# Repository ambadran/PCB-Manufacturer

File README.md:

# PCB-Manufacturer

###  Intro
A cnc machine with a kinematic mounting mechanism and specialised code to change head as wanted so as to have access to all the
tools to create a PCB without any human intervention.

### Mechanics
This is a 3 Axis CNC machine made of both metal and 3D printed Parts.
The main driving mechanism is a V-wheel on 2020 profile system with a GT-2 belt driving.
Nema17 Motors was used. The machine was designed for maximal repeatability. 

A 3D printed Kinematic Mounting System was developed to enable the CNC machine to detach and attach to different tool heads on command. The current tool heads are a laser head, a spindle, a Pen marker. The machine automatically attaches to the wanted tool heads without any human intervention.

I also developed an auto-clamping system that clamps the PCB in the bed automatically.

#### Photos

### Electronics
The Main MCU is an Arduino Mega. A Custom GRBL firmware created by me is running on it.

To add a screen monitoring functionality and control the main MCU wirelessly through WiFi, I added a raspberry pi 4 with a 7 inch screen, running mainly UGS Software to monitor the CNC machine.

The Stepper drivers are powerful TB6600 drivers, The end-stops have their own opto-coupler circuit. 
There are 3 power supplies for the CNC machine. one 5v for the main MCU only, one 5v for the raspberry pi. and the third 24v is for the rest of the CNC machine.

This main 24v power supply is switched on using a relay that is controled by the Main MCU. A special G-Code was coded in the firmware to control the main power supply. This adds an important safety layer as the machine is intended to be run remotely.

To relieve the Main MCU from doing everything in the project. I took the liberity to make different circuits for different functions needed for this machine.

I developed a circuit that takes in a 3-bit binary code and the spindle PWM signal from the Main MCU. Then it decodes the 3-bit binary code to allow the PWM to exit through one of the 8 channels that this CNC machine controls. Meaning, the machine can control 8 different end-effectors with PWM, depending on the current 3-bit binary that the MCU outputs.

Another circuit worth mentioning was the stand alone circuit to control the latching mechanism of the kinematic mounting system, where the input to the circuit is just a HIGH/LOW signal from the main MCU triggered by a G-code command `A1` or `A0`. The local MCU does controls the unipolar stepper to latch ON or OFF to the Female kinematic mounts on command and does all the necessary closed-loop logic locally.

### Programming
I customized the GRBL firmware from: https://github.com/gnea/grbl 
To accomodate for all the new functionality needed for this CNC machine.
I put in my own G-code commands like `A<x>`, `B<x>` or `C<x>`, that outputs the necessary logic on the Main MCU GPIOs, with no compromise to the original code.

I also developed (from scratch) a complete CAM solution that takes in the gerber files and gives out the G-code ready for my machine. However, due to me deciding to develop from scratch and not use geometry-manipulating libraries like `shapely`. There is alot of corner cases that this version can't handle. 
However, I developed V2 of my all-in-one CAM solution for my CNC machine here: https://github.com/ambadran/PCB-CAM

This version is much much more reliable as to it not being built from scratch.

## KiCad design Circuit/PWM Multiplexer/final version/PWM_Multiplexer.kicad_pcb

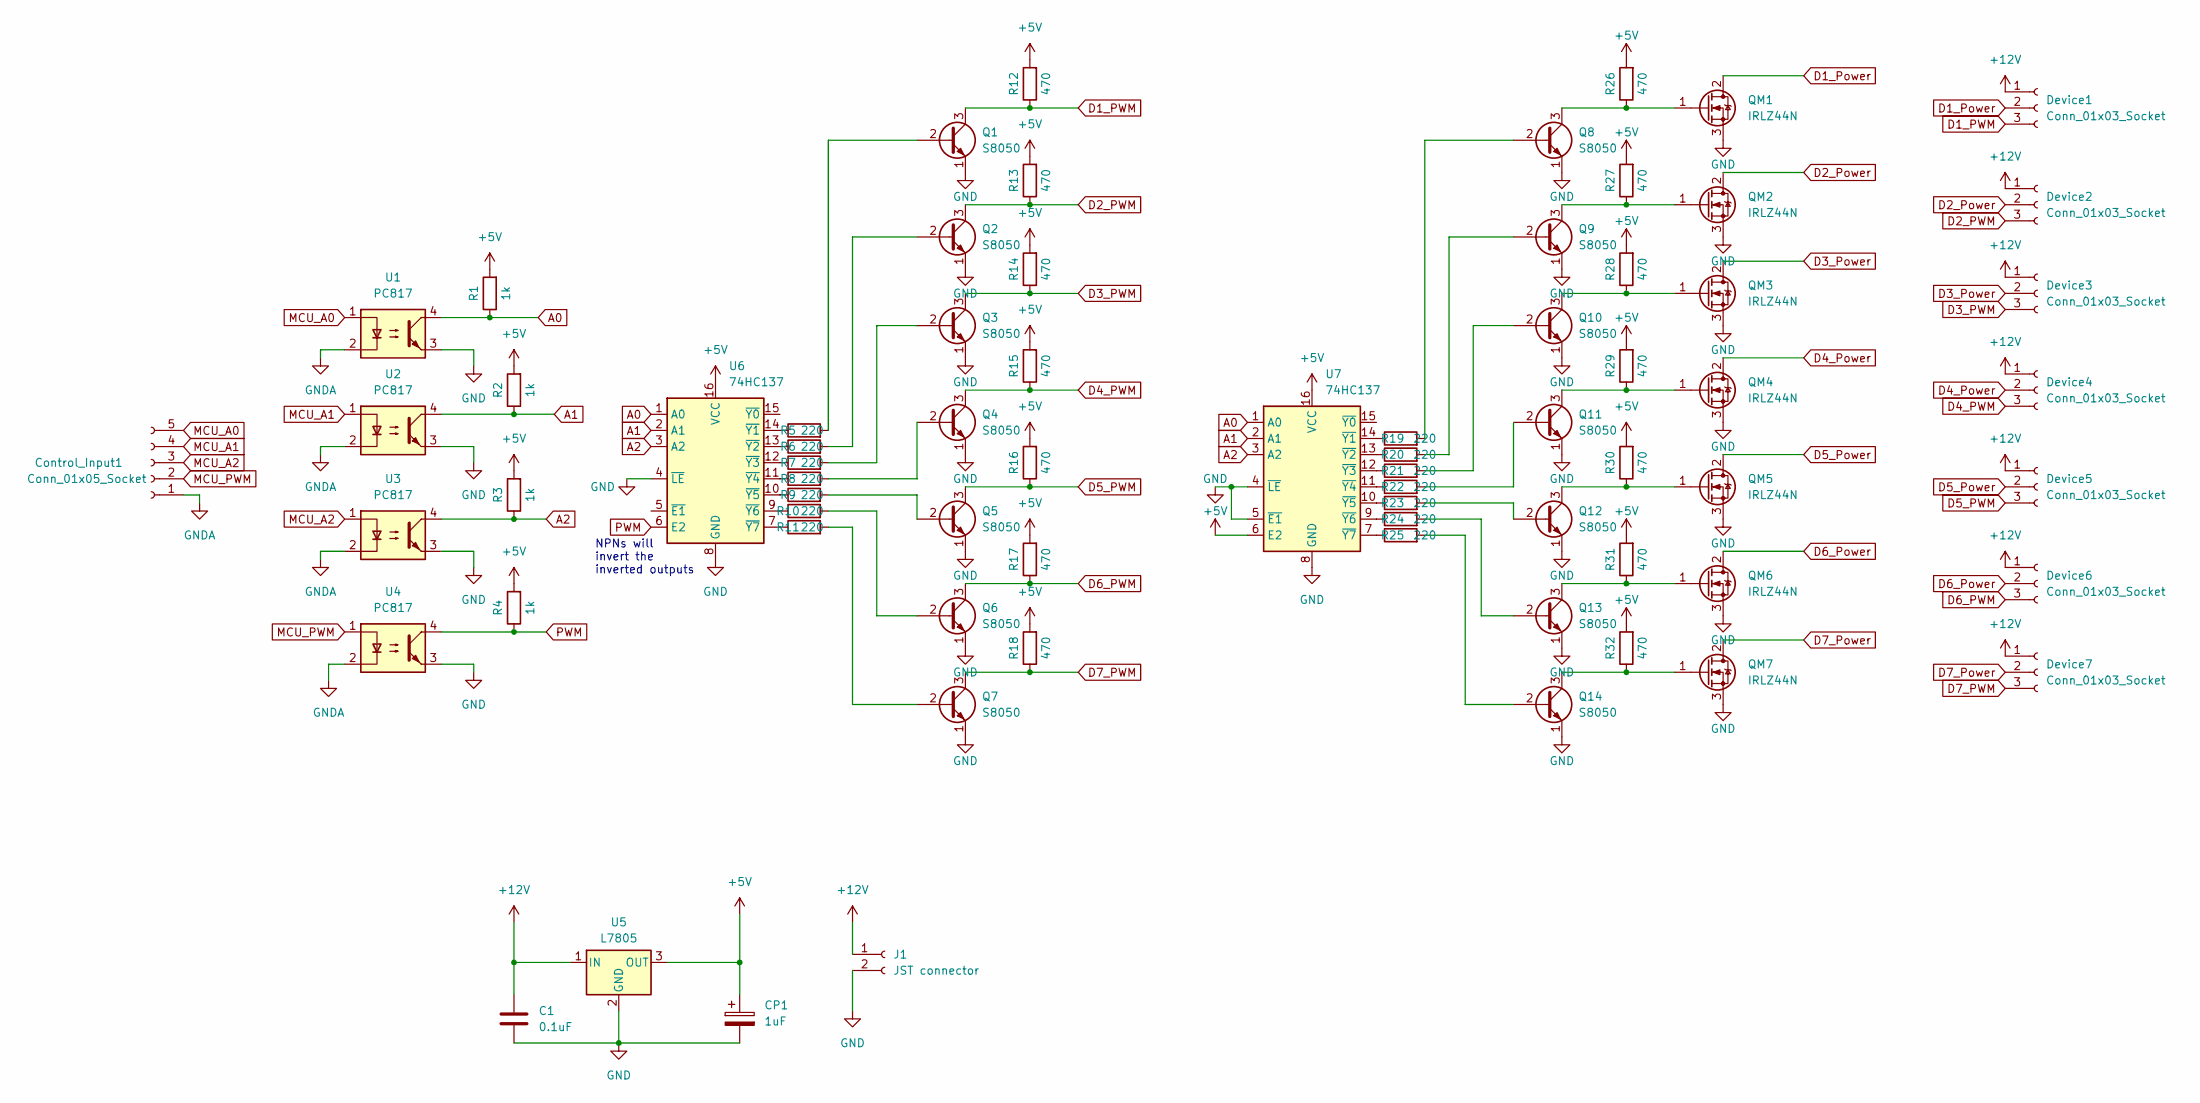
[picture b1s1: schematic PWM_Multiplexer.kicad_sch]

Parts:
C1: 0.1uF; C_Disc_D5.0mm_W2.5mm_P2.50mm
CP1: 1uF; CP_Radial_D5.0mm_P2.50mm
Control_Input1: Conn_01x05_Socket; JST_EH_S5B-EH_1x05_P2.50mm_Horizontal
Device1, Device2, Device3, Device4, Device5, Device6, Device7: Conn_01x03_Socket; JST_EH_S3B-EH_1x03_P2.50mm_Horizontal
J1: JST connector; JST_EH_S2B-EH_1x02_P2.50mm_Horizontal
Q1, Q2, Q3, Q4, Q5, Q6, Q7, Q8, Q9, Q10, Q11, Q12, Q13, Q14: S8050; TO-92_Inline
QM1, QM2, QM3, QM4, QM5, QM6, QM7: IRLZ44N; TO-220-3_Vertical
R1, R2, R3, R4: 1k; R_Axial_DIN0207_L6.3mm_D2.5mm_P7.62mm_Horizontal
R5, R6, R7, R8, R9, R10, R11: 220; R_Axial_DIN0207_L6.3mm_D2.5mm_P10.16mm_Horizontal
R12, R13, R14, R15, R16, R17, R18: 470; R_Axial_DIN0207_L6.3mm_D2.5mm_P7.62mm_Horizontal
R19, R20, R21, R22, R23, R24, R25: 220; R_Axial_DIN0207_L6.3mm_D2.5mm_P7.62mm_Horizontal
R26, R27, R28, R29, R30, R31, R32: 470; R_Axial_DIN0207_L6.3mm_D2.5mm_P10.16mm_Horizontal
U1, U2, U3, U4: PC817; DIP-4_W7.62mm
U5: L7805; TO-220-3_Vertical
U6, U7: 74HC137; DIP-16_W7.62mm_Socket_LongPads

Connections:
+5V: CP1.1, R1.2, R2.2, R3.2, R4.2, R12.2, R13.2, R14.2, R15.2, R16.2, R17.2, R18.2, R26.2, R27.2, R28.2, R29.2, R30.2, R31.2, R32.2, U5.3 (OUT), U6.16 (VCC), U7.6 (E2), U7.16 (VCC)
+12V: C1.1, Device1.1, Device2.1, Device3.1, Device4.1, Device5.1, Device6.1, Device7.1, J1.1, U5.1 (IN)
A0: R1.1, U1.4, U6.1 (A0), U7.1 (A0)
A1: R2.1, U2.4, U6.2 (A1), U7.2 (A1)
A2: R3.1, U3.4, U6.3 (A2), U7.3 (A2)
D1_PWM: Device1.3, Q1.3 (C), R12.1
D1_Power: Device1.2, QM1.2 (D)
D2_PWM: Device2.3, Q2.3 (C), R13.1
D2_Power: Device2.2, QM2.2 (D)
D3_PWM: Device3.3, Q3.3 (C), R14.1
D3_Power: Device3.2, QM3.2 (D)
D4_PWM: Device4.3, Q4.3 (C), R15.1
D4_Power: Device4.2, QM4.2 (D)
D5_PWM: Device5.3, Q5.3 (C), R16.1
D5_Power: Device5.2, QM5.2 (D)
D6_PWM: Device6.3, Q6.3 (C), R17.1
D6_Power: Device6.2, QM6.2 (D)
D7_PWM: Device7.3, Q7.3 (C), R18.1
D7_Power: Device7.2, QM7.2 (D)
GND: C1.2, CP1.2, J1.2, Q1.1 (E), Q2.1 (E), Q3.1 (E), Q4.1 (E), Q5.1 (E), Q6.1 (E), Q7.1 (E), Q8.1 (E), Q9.1 (E), Q10.1 (E), Q11.1 (E), Q12.1 (E), Q13.1 (E), Q14.1 (E), QM1.3 (S), QM2.3 (S), QM3.3 (S), QM4.3 (S), QM5.3 (S), QM6.3 (S), QM7.3 (S), U1.3, U2.3, U3.3, U4.3, U5.2 (GND), U6.4 (~LE), U6.8 (GND), U7.4 (~LE), U7.5 (~E1), U7.8 (GND)
GNDA: Control_Input1.1, U1.2, U2.2, U3.2, U4.2
MCU_A0: Control_Input1.5, U1.1
MCU_A1: Control_Input1.4, U2.1
MCU_A2: Control_Input1.3, U3.1
MCU_PWM: Control_Input1.2, U4.1
unnamed: Q1.2 (B), R5.2
unnamed: Q2.2 (B), R6.2
unnamed: Q3.2 (B), R7.2
unnamed: Q4.2 (B), R8.2
unnamed: Q5.2 (B), R9.2
unnamed: Q6.2 (B), R10.2
unnamed: Q7.2 (B), R11.2
unnamed: Q8.2 (B), R19.2
unnamed: Q8.3 (C), QM1.1 (G), R26.1
unnamed: Q9.2 (B), R20.2
unnamed: Q9.3 (C), QM2.1 (G), R27.1
unnamed: Q10.2 (B), R21.2
unnamed: Q10.3 (C), QM3.1 (G), R28.1
unnamed: Q11.2 (B), R22.2
unnamed: Q11.3 (C), QM4.1 (G), R29.1
unnamed: Q12.2 (B), R23.2
unnamed: Q12.3 (C), QM5.1 (G), R30.1
unnamed: Q13.2 (B), R24.2
unnamed: Q13.3 (C), QM6.1 (G), R31.1
unnamed: Q14.2 (B), R25.2
unnamed: Q14.3 (C), QM7.1 (G), R32.1
unnamed: R5.1, U6.14 (~Y1)
unnamed: R6.1, U6.13 (~Y2)
unnamed: R7.1, U6.12 (~Y3)
unnamed: R8.1, U6.11 (~Y4)
unnamed: R9.1, U6.10 (~Y5)
unnamed: R10.1, U6.9 (~Y6)
unnamed: R11.1, U6.7 (~Y7)
unnamed: R19.1, U7.14 (~Y1)
unnamed: R20.1, U7.13 (~Y2)
unnamed: R21.1, U7.12 (~Y3)
unnamed: R22.1, U7.11 (~Y4)
unnamed: R23.1, U7.10 (~Y5)
unnamed: R24.1, U7.9 (~Y6)
unnamed: R25.1, U7.7 (~Y7)
PWM: R4.1, U4.4, U6.6 (E2)

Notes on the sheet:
NPNs will invert the inverted outputs

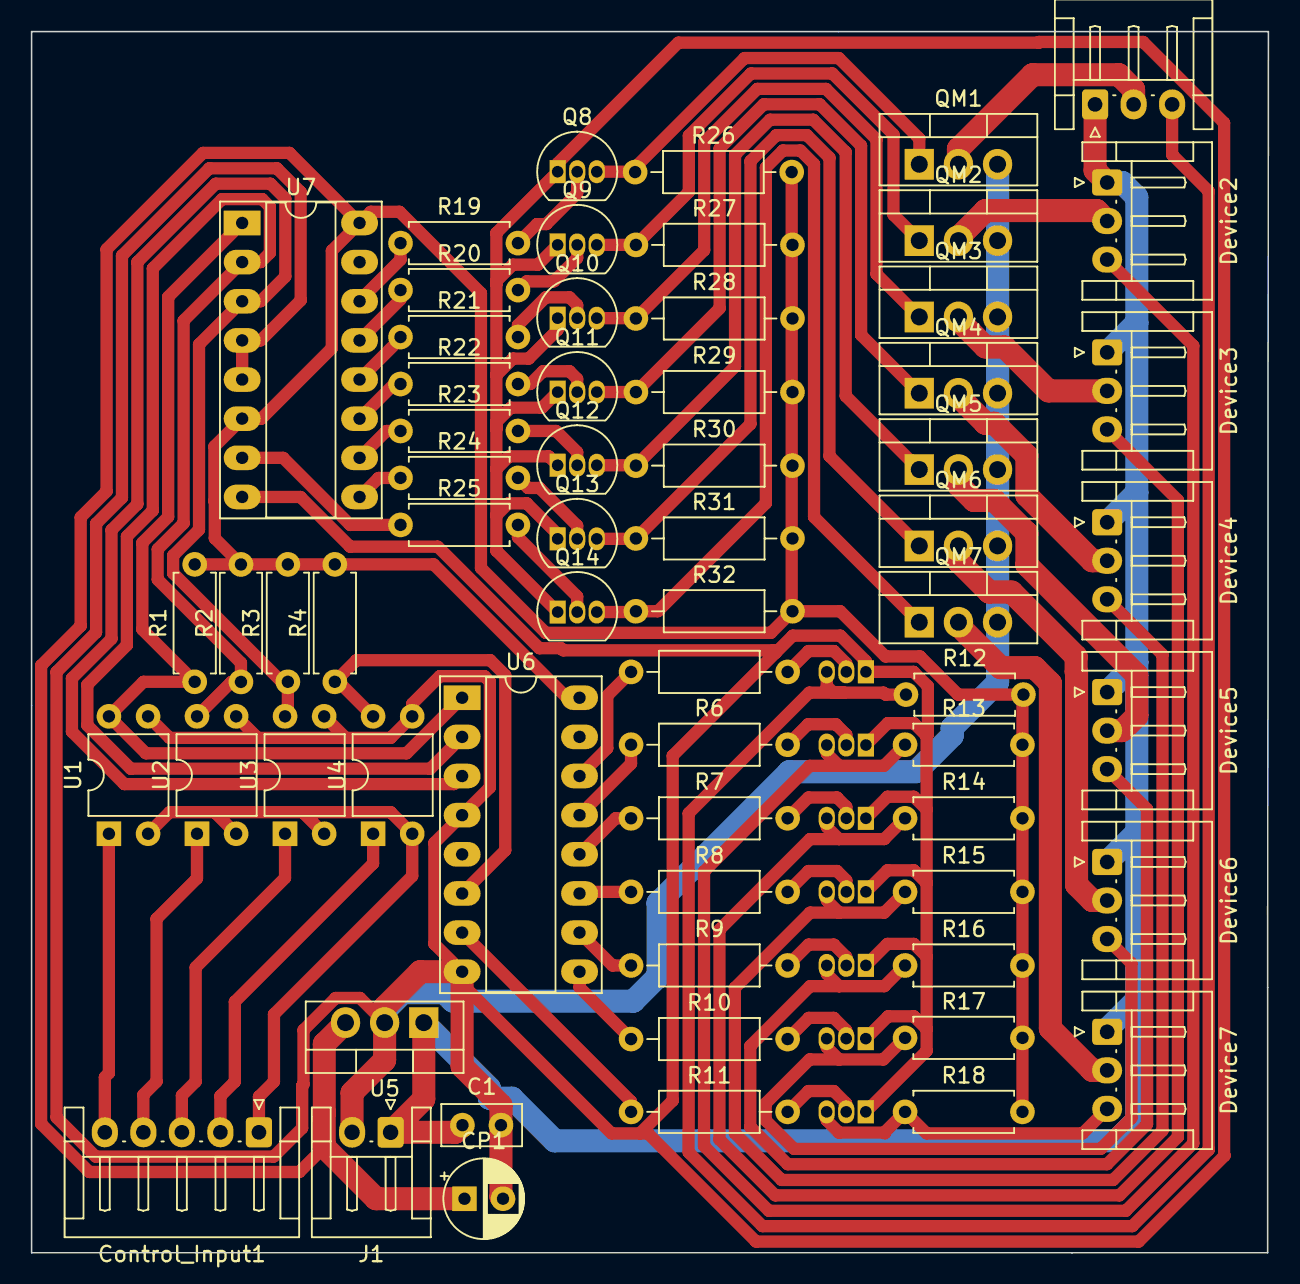
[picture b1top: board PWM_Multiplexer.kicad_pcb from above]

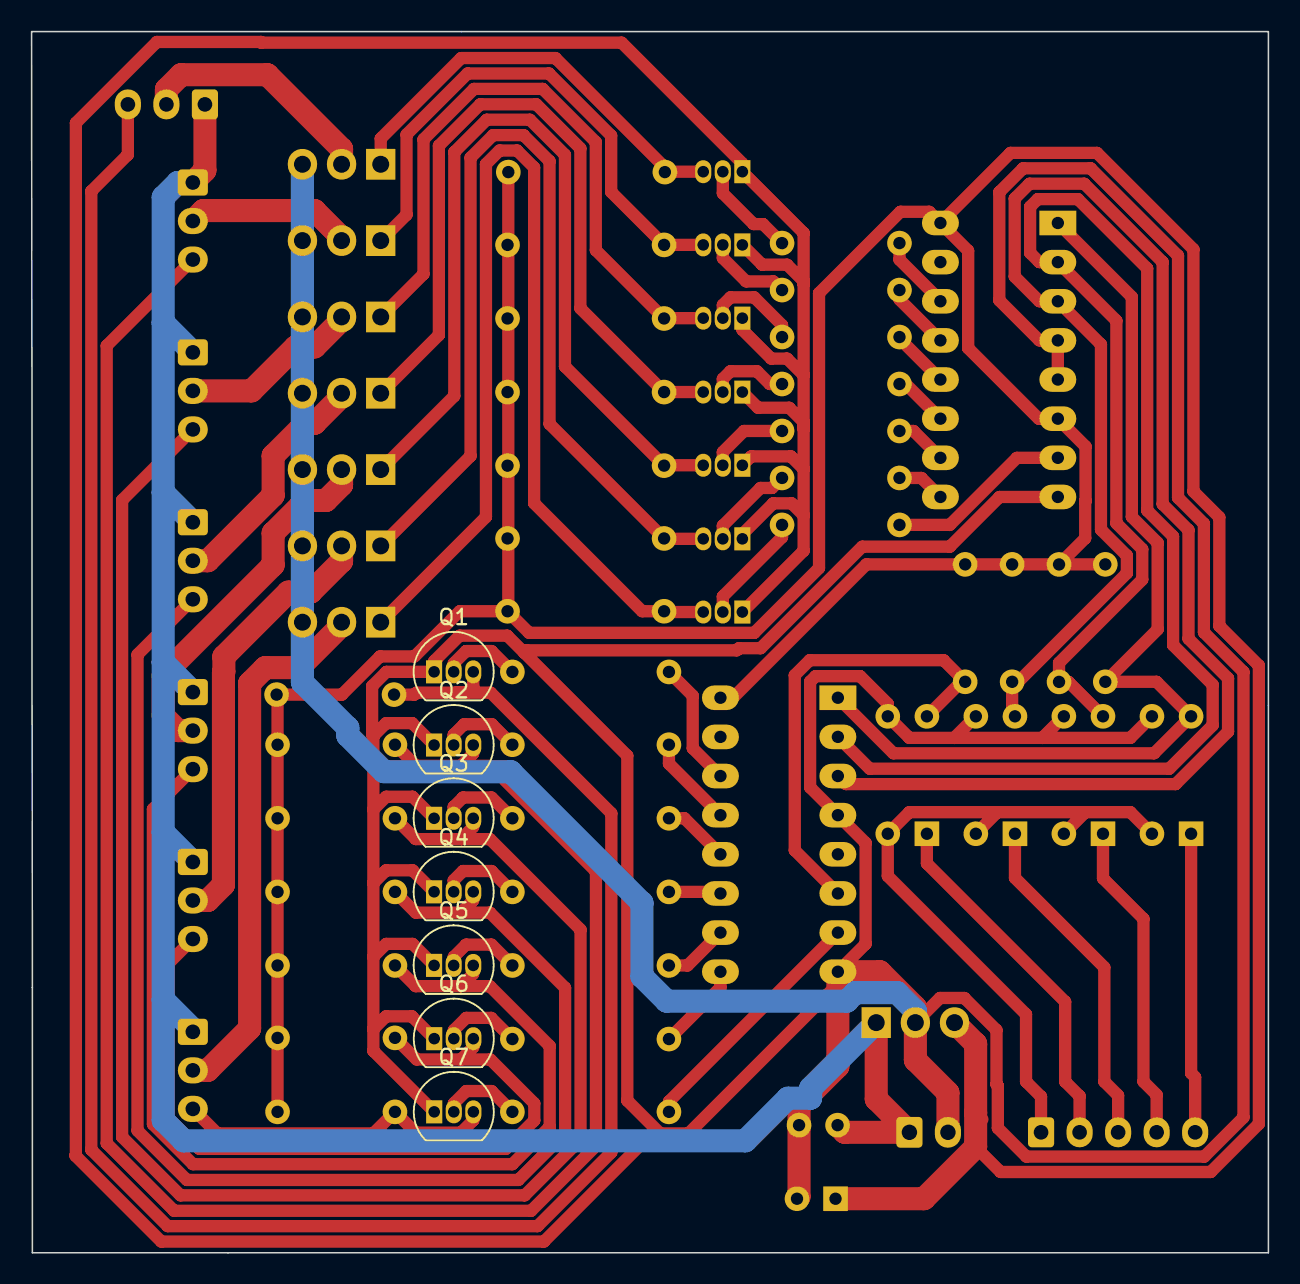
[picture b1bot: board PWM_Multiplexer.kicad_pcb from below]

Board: 2 copper layers, 80.3 x 79.2 mm, 71 parts (7 on the bottom side), 61 nets.

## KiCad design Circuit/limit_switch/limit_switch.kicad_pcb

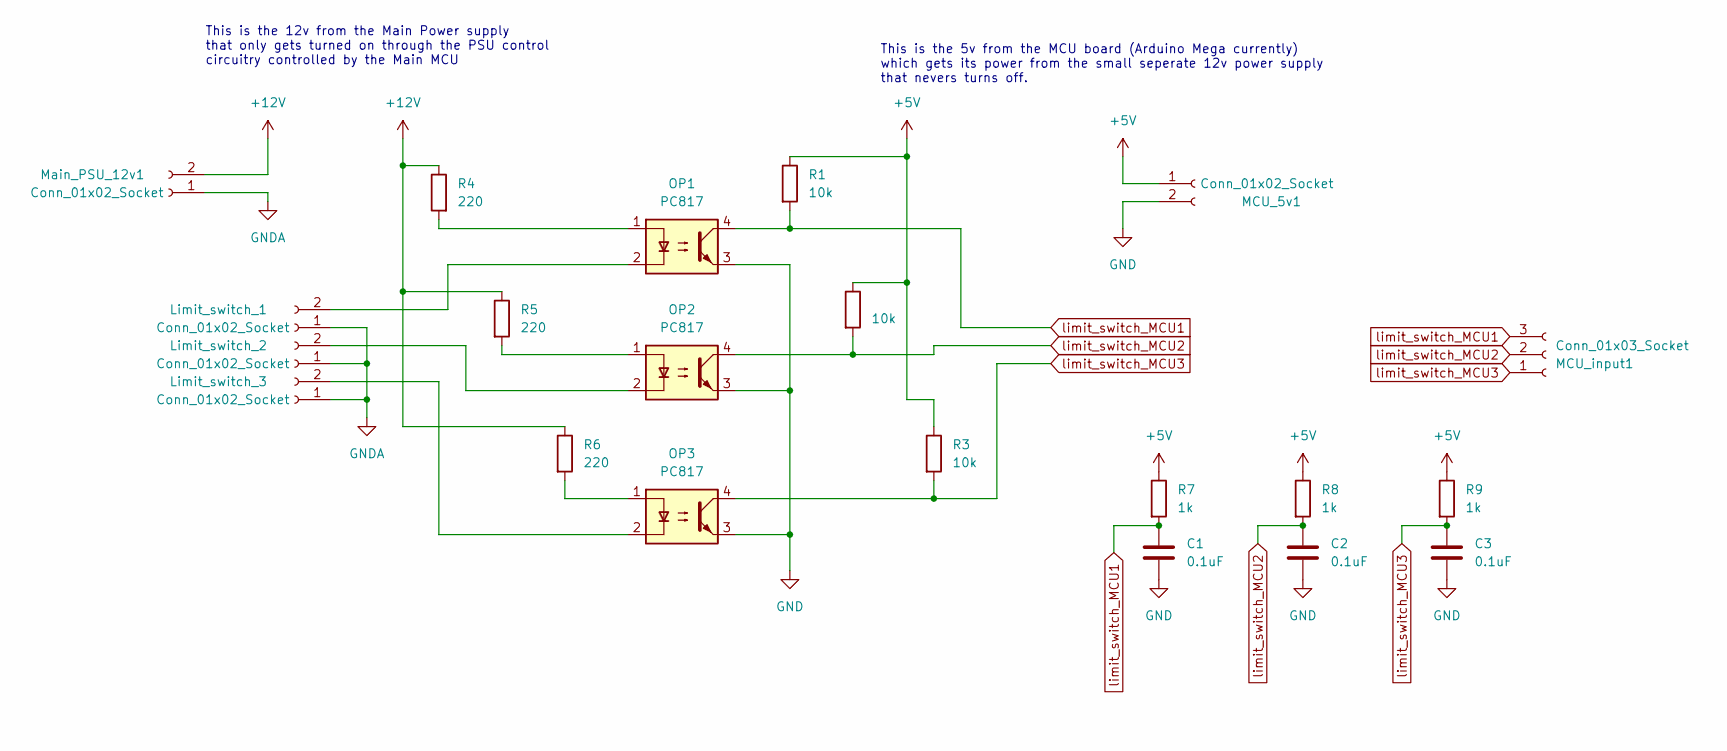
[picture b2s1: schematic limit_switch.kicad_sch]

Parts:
C1, C2, C3: 0.1uF; C_Disc_D5.0mm_W2.5mm_P5.00mm
Limit_switch_1, Limit_switch_2, Limit_switch_3: Conn_01x02_Socket; JST_EH_S2B-EH_1x02_P2.50mm_Horizontal
MCU_5v1: Conn_01x02_Socket; JST_EH_S2B-EH_1x02_P2.50mm_Horizontal
MCU_input1: Conn_01x03_Socket; JST_EH_S3B-EH_1x03_P2.50mm_Horizontal
Main_PSU_12v1: Conn_01x02_Socket; JST_EH_S2B-EH_1x02_P2.50mm_Horizontal
OP1, OP2, OP3: PC817; DIP-4_W7.62mm
R1, R2, R3: 10k; R_Axial_DIN0207_L6.3mm_D2.5mm_P7.62mm_Horizontal
R4, R5, R6: 220; R_Axial_DIN0207_L6.3mm_D2.5mm_P7.62mm_Horizontal
R7, R8, R9: 1k; R_Axial_DIN0207_L6.3mm_D2.5mm_P7.62mm_Horizontal

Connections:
+5V: MCU_5v1.1, R1.1, R2.1, R3.1, R7.1, R8.1, R9.1
+12V: Main_PSU_12v1.2, R4.1, R5.1, R6.1
GND: C1.2, C2.2, C3.2, MCU_5v1.2, OP1.3, OP2.3, OP3.3
GNDA: Limit_switch_1.1, Limit_switch_2.1, Limit_switch_3.1, Main_PSU_12v1.1
unnamed: Limit_switch_1.2, OP1.2
unnamed: Limit_switch_2.2, OP2.2
unnamed: Limit_switch_3.2, OP3.2
unnamed: OP1.1, R4.2
unnamed: OP2.1, R5.2
unnamed: OP3.1, R6.2
limit_switch_MCU1: C1.1, MCU_input1.3, OP1.4, R1.2, R7.2
limit_switch_MCU2: C2.1, MCU_input1.2, OP2.4, R2.2, R8.2
limit_switch_MCU3: C3.1, MCU_input1.1, OP3.4, R3.2, R9.2

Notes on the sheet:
This is the 12v from the Main Power supply that only gets turned on through the PSU control circuitry controlled by the Main MCU
This is the 5v from the MCU board (Arduino Mega currently) which gets its power from the small seperate 12v power supply that nevers turns off.

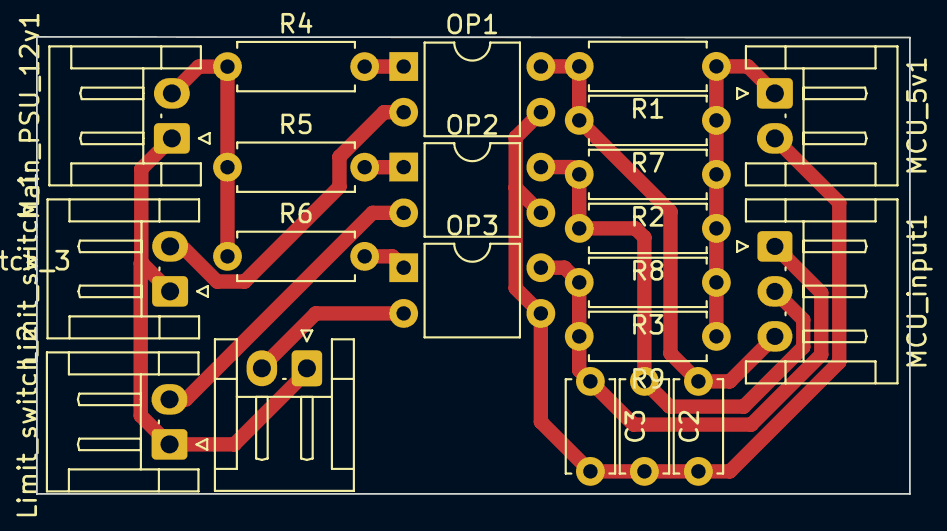
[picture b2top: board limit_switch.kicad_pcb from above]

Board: 2 copper layers, 48.5 x 25.4 mm, 21 parts (0 on the bottom side), 13 nets.

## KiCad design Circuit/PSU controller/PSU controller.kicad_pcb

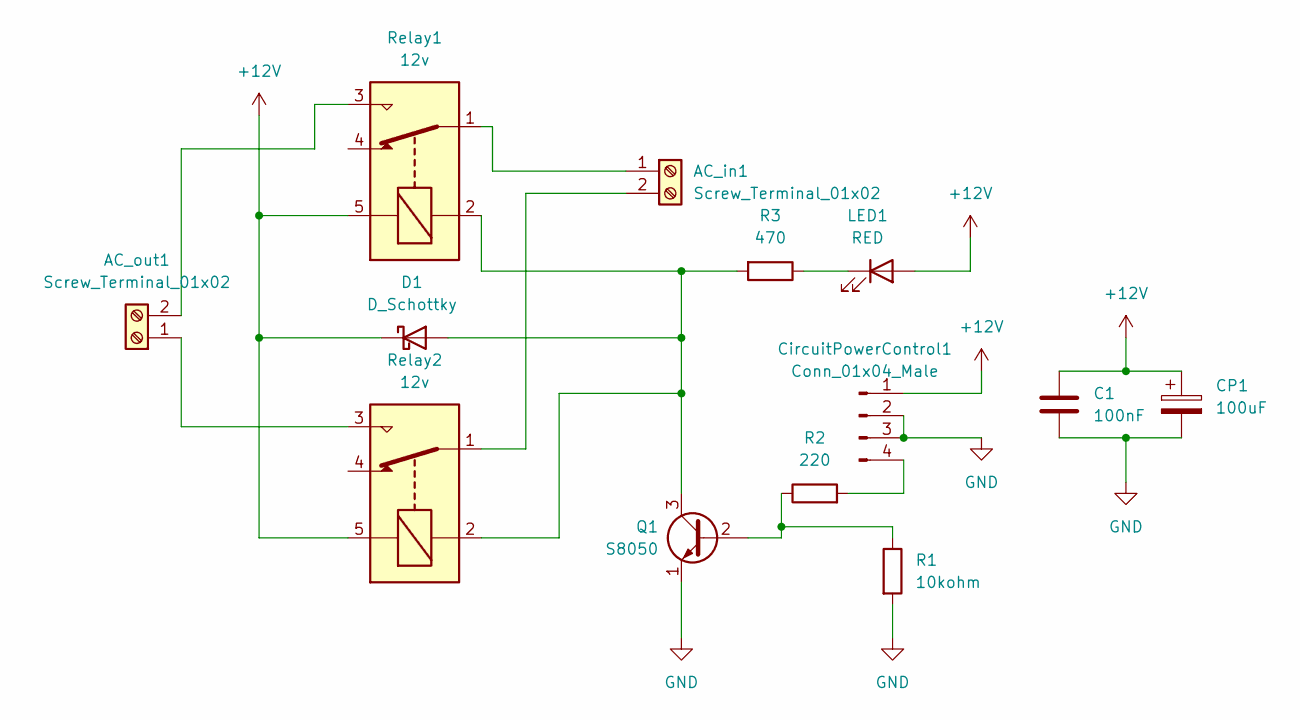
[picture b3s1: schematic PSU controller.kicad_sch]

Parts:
AC_in1: Screw_Terminal_01x02; TerminalBlock_bornier-2_P5.08mm
AC_out1: Screw_Terminal_01x02; TerminalBlock_bornier-2_P5.08mm
C1: 100nF; C_Disc_D5.0mm_W2.5mm_P2.50mm
CP1: 100uF; CP_Radial_D5.0mm_P2.00mm
CircuitPowerControl1: Conn_01x04_Male; PinSocket_1x04_P2.54mm_Vertical
D1: D_Schottky; D_DO-34_SOD68_P7.62mm_Horizontal
LED1: RED; D_A-405_P2.54mm_Vertical_AnodeUp
Q1: S8050; TO-92_Inline
R1: 10kohm; R_Axial_DIN0207_L6.3mm_D2.5mm_P7.62mm_Horizontal
R2: 220; R_Axial_DIN0207_L6.3mm_D2.5mm_P7.62mm_Horizontal
R3: 470; R_Axial_DIN0207_L6.3mm_D2.5mm_P7.62mm_Horizontal
Relay1, Relay2: 12v; Relay_SPDT_SANYOU_SRD_Series_Form_C

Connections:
+12V: C1.1, CP1.1, CircuitPowerControl1.1, D1.1 (K), LED1.2 (A), Relay1.5, Relay2.5
GND: C1.2, CP1.2, CircuitPowerControl1.2, CircuitPowerControl1.3, Q1.1 (E), R1.2
unnamed: AC_in1.1, Relay1.1
unnamed: AC_in1.2, Relay2.1
unnamed: AC_out1.1, Relay2.3
unnamed: AC_out1.2, Relay1.3
unnamed: CircuitPowerControl1.4, R2.2
unnamed: D1.2 (A), Q1.3 (C), R3.2, Relay1.2, Relay2.2
unnamed: LED1.1 (K), R3.1
unnamed: Q1.2 (B), R1.1, R2.1

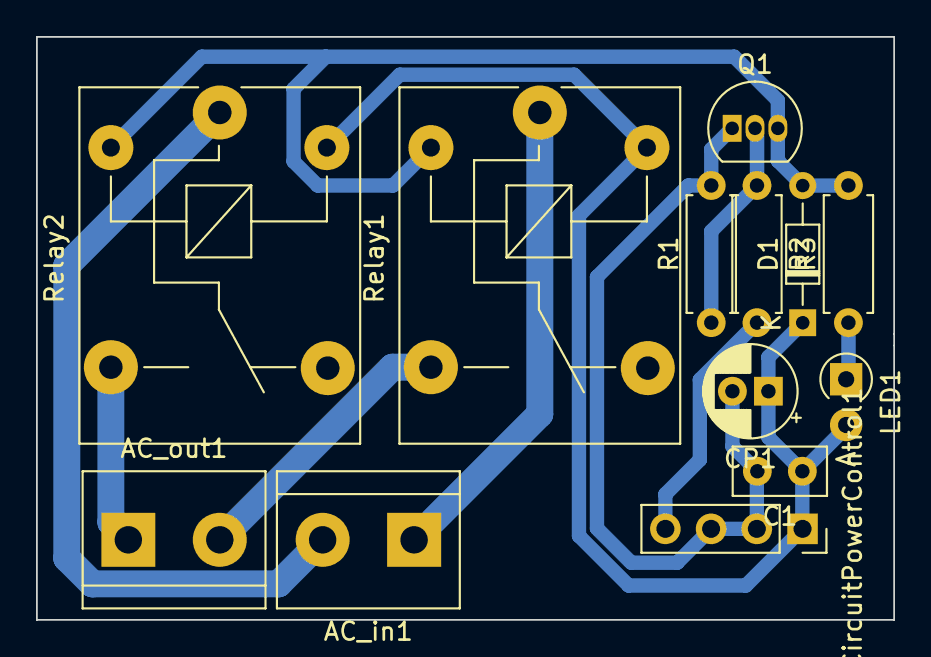
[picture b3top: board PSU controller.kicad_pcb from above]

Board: 2 copper layers, 47.6 x 32.4 mm, 13 parts (0 on the bottom side), 10 nets.

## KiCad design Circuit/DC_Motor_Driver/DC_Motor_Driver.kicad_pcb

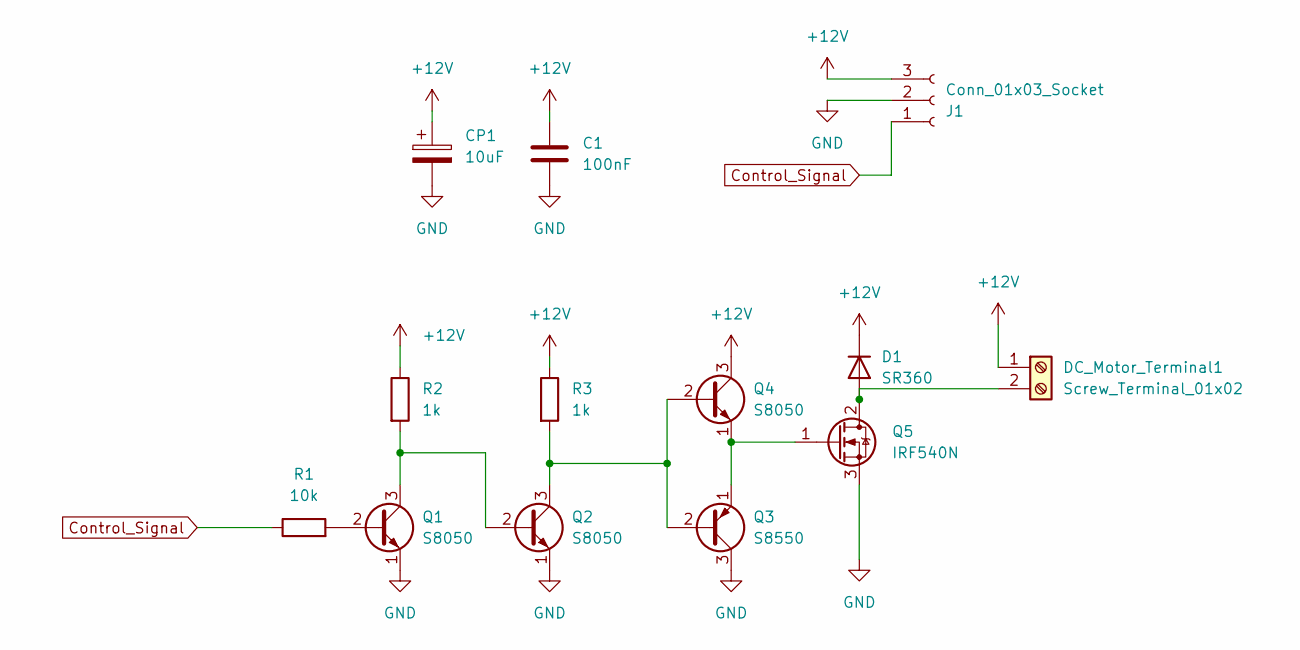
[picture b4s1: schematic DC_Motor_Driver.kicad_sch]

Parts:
C1: 100nF; C_Disc_D5.0mm_W2.5mm_P2.50mm
CP1: 10uF; CP_Radial_D5.0mm_P2.50mm
D1: SR360; D_DO-27_P12.70mm_Horizontal
DC_Motor_Terminal1: Screw_Terminal_01x02; TerminalBlock_bornier-2_P5.08mm
J1: Conn_01x03_Socket; JST_EH_S3B-EH_1x03_P2.50mm_Horizontal
Q1, Q2, Q4: S8050; TO-92_Inline
Q3: S8550; TO-92_Inline
Q5: IRF540N; TO-220-3_Vertical
R1: 10k; R_Axial_DIN0207_L6.3mm_D2.5mm_P7.62mm_Horizontal
R2, R3: 1k; R_Axial_DIN0207_L6.3mm_D2.5mm_P7.62mm_Horizontal

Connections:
+12V: C1.1, CP1.1, D1.1 (K), DC_Motor_Terminal1.1, J1.3, Q4.3 (C), R2.1, R3.1
Control_Signal: J1.1, R1.1
GND: C1.2, CP1.2, J1.2, Q1.1 (E), Q2.1 (E), Q3.3 (C), Q5.3 (S)
unnamed: D1.2 (A), DC_Motor_Terminal1.2, Q5.2 (D)
unnamed: Q1.2 (B), R1.2
unnamed: Q1.3 (C), Q2.2 (B), R2.2
unnamed: Q2.3 (C), Q3.2 (B), Q4.2 (B), R3.2
unnamed: Q3.1 (E), Q4.1 (E), Q5.1 (G)

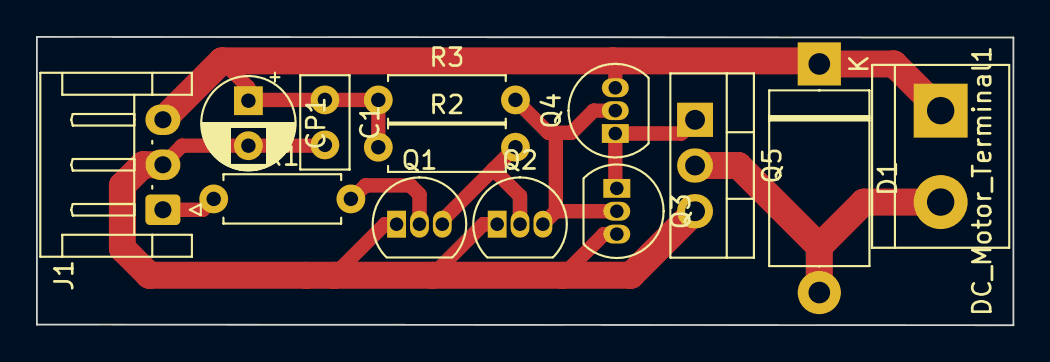
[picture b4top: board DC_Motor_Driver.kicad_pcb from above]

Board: 2 copper layers, 54.2 x 16.0 mm, 13 parts (0 on the bottom side), 8 nets.

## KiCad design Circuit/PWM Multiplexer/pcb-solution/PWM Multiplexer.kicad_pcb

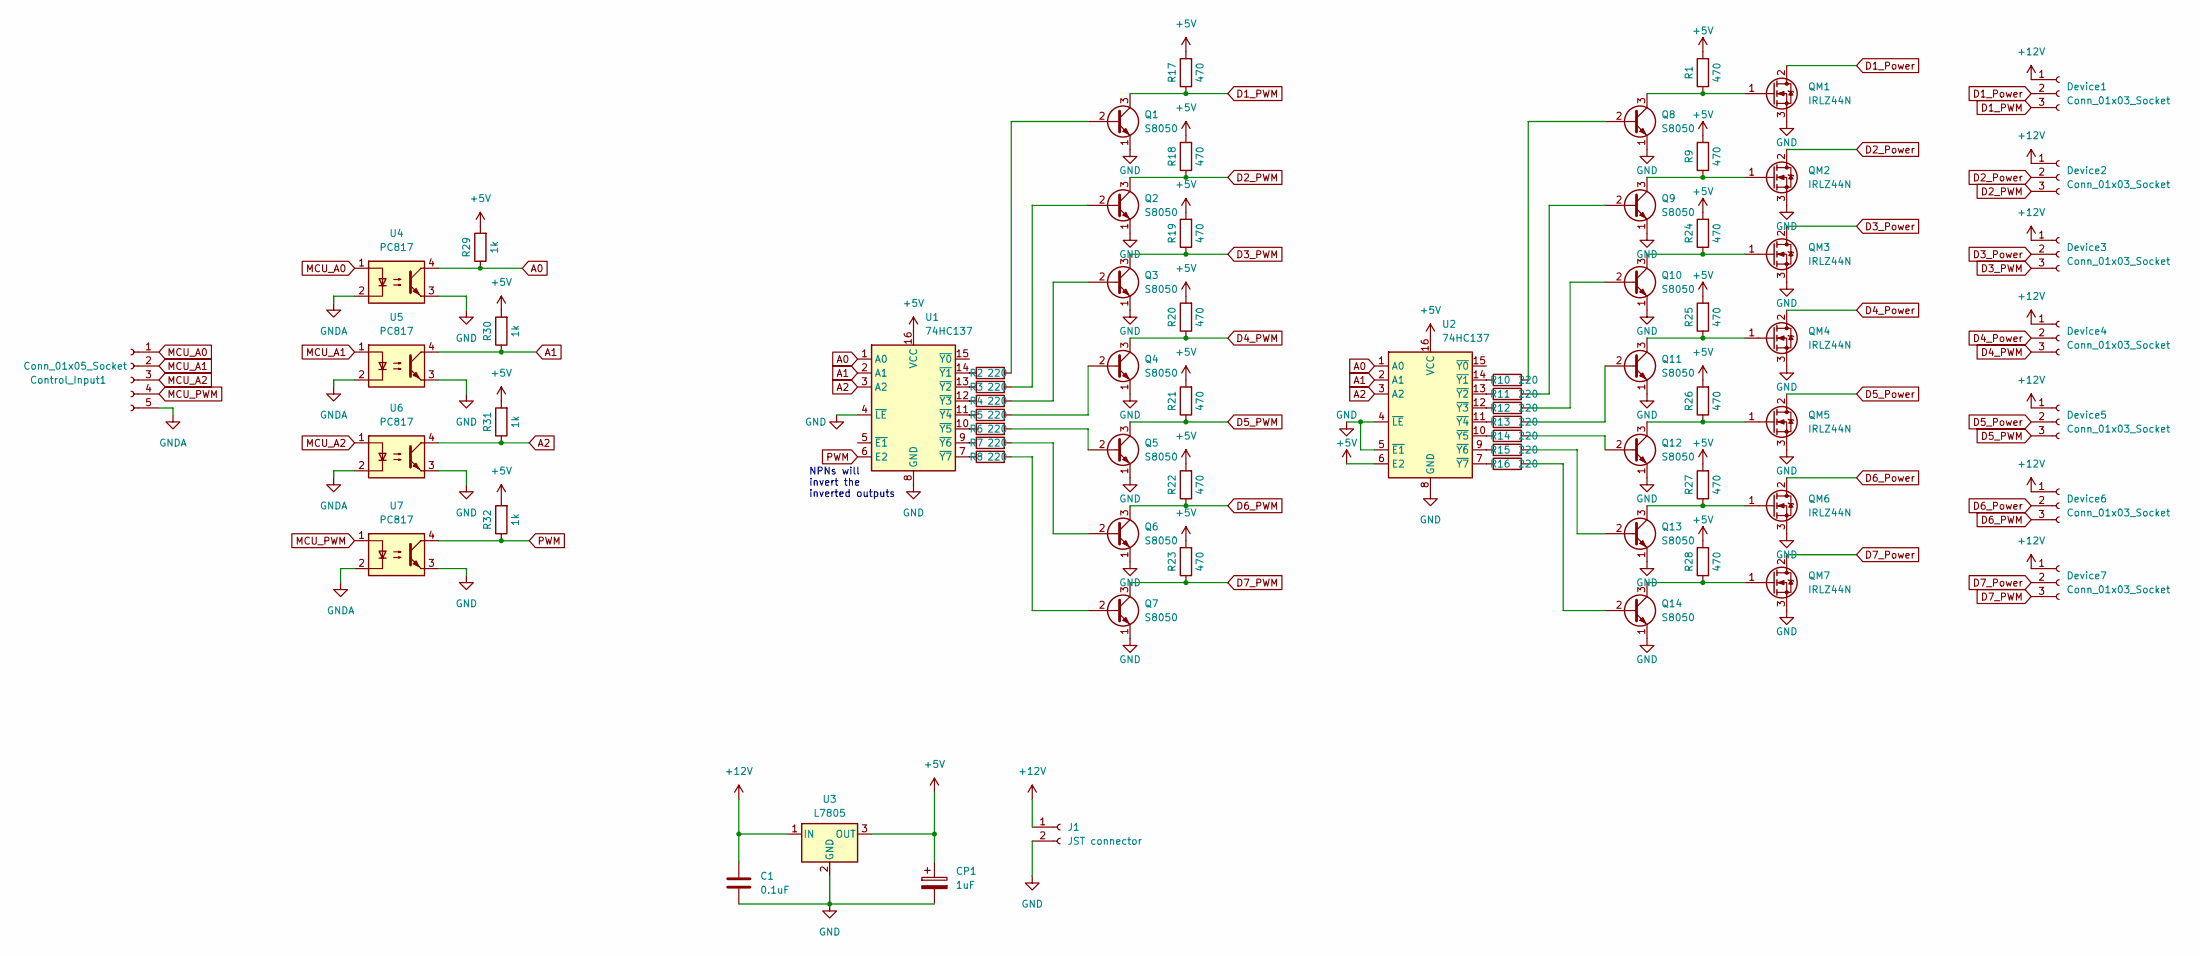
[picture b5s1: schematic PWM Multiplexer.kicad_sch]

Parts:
C1: 0.1uF; C_Disc_D5.0mm_W2.5mm_P2.50mm
CP1: 1uF; CP_Radial_D5.0mm_P2.50mm
Control_Input1: Conn_01x05_Socket; PinSocket_1x05_P2.54mm_Horizontal
Device1, Device2, Device3, Device4, Device5, Device6, Device7: Conn_01x03_Socket; PinSocket_1x03_P2.54mm_Horizontal
J1: JST connector; JST_EH_S2B-EH_1x02_P2.50mm_Horizontal
Q1, Q2, Q3, Q4, Q5, Q6, Q7, Q8, Q9, Q10, Q11, Q12, Q13, Q14: S8050; TO-92_Inline
QM1, QM2, QM3, QM4, QM5, QM6, QM7: IRLZ44N; TO-220-3_Vertical
R1, R9, R17, R18, R19, R20, R21, R22, R23, R24, R25, R26, R27, R28: 470; R_Axial_DIN0207_L6.3mm_D2.5mm_P10.16mm_Horizontal
R2, R3, R4, R5, R6, R7, R8, R10, R11, R12, R13, R14, R15, R16: 220; R_Axial_DIN0207_L6.3mm_D2.5mm_P7.62mm_Horizontal
R29, R30, R31, R32: 1k; R_Axial_DIN0207_L6.3mm_D2.5mm_P10.16mm_Horizontal
U1, U2: 74HC137; DIP-16_W7.62mm_Socket_LongPads
U3: L7805; TO-220-3_Vertical
U4, U5, U6, U7: PC817; DIP-4_W7.62mm

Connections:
+5V: CP1.1, R1.2, R9.2, R17.2, R18.2, R19.2, R20.2, R21.2, R22.2, R23.2, R24.2, R25.2, R26.2, R27.2, R28.2, R29.2, R30.2, R31.2, R32.2, U1.16 (VCC), U2.6 (E2), U2.16 (VCC), U3.3 (OUT)
+12V: C1.1, Device1.1, Device2.1, Device3.1, Device4.1, Device5.1, Device6.1, Device7.1, J1.1, U3.1 (IN)
A0: R29.1, U1.1 (A0), U2.1 (A0), U4.4
A1: R30.1, U1.2 (A1), U2.2 (A1), U5.4
A2: R31.1, U1.3 (A2), U2.3 (A2), U6.4
D1_PWM: Device1.3, Q1.3 (C), R17.1
D1_Power: Device1.2, QM1.2 (D)
D2_PWM: Device2.3, Q2.3 (C), R18.1
D2_Power: Device2.2, QM2.2 (D)
D3_PWM: Device3.3, Q3.3 (C), R19.1
D3_Power: Device3.2, QM3.2 (D)
D4_PWM: Device4.3, Q4.3 (C), R20.1
D4_Power: Device4.2, QM4.2 (D)
D5_PWM: Device5.3, Q5.3 (C), R21.1
D5_Power: Device5.2, QM5.2 (D)
D6_PWM: Device6.3, Q6.3 (C), R22.1
D6_Power: Device6.2, QM6.2 (D)
D7_PWM: Device7.3, Q7.3 (C), R23.1
D7_Power: Device7.2, QM7.2 (D)
GND: C1.2, CP1.2, J1.2, Q1.1 (E), Q2.1 (E), Q3.1 (E), Q4.1 (E), Q5.1 (E), Q6.1 (E), Q7.1 (E), Q8.1 (E), Q9.1 (E), Q10.1 (E), Q11.1 (E), Q12.1 (E), Q13.1 (E), Q14.1 (E), QM1.3 (S), QM2.3 (S), QM3.3 (S), QM4.3 (S), QM5.3 (S), QM6.3 (S), QM7.3 (S), U1.4 (~LE), U1.8 (GND), U2.4 (~LE), U2.5 (~E1), U2.8 (GND), U3.2 (GND), U4.3, U5.3, U6.3, U7.3
GNDA: Control_Input1.5, U4.2, U5.2, U6.2, U7.2
MCU_A0: Control_Input1.1, U4.1
MCU_A1: Control_Input1.2, U5.1
MCU_A2: Control_Input1.3, U6.1
MCU_PWM: Control_Input1.4, U7.1
unnamed: Q1.2 (B), R2.2
unnamed: Q2.2 (B), R3.2
unnamed: Q3.2 (B), R4.2
unnamed: Q4.2 (B), R5.2
unnamed: Q5.2 (B), R6.2
unnamed: Q6.2 (B), R7.2
unnamed: Q7.2 (B), R8.2
unnamed: Q8.2 (B), R10.2
unnamed: Q8.3 (C), QM1.1 (G), R1.1
unnamed: Q9.2 (B), R11.2
unnamed: Q9.3 (C), QM2.1 (G), R9.1
unnamed: Q10.2 (B), R12.2
unnamed: Q10.3 (C), QM3.1 (G), R24.1
unnamed: Q11.2 (B), R13.2
unnamed: Q11.3 (C), QM4.1 (G), R25.1
unnamed: Q12.2 (B), R14.2
unnamed: Q12.3 (C), QM5.1 (G), R26.1
unnamed: Q13.2 (B), R15.2
unnamed: Q13.3 (C), QM6.1 (G), R27.1
unnamed: Q14.2 (B), R16.2
unnamed: Q14.3 (C), QM7.1 (G), R28.1
unnamed: R2.1, U1.14 (~Y1)
unnamed: R3.1, U1.13 (~Y2)
unnamed: R4.1, U1.12 (~Y3)
unnamed: R5.1, U1.11 (~Y4)
unnamed: R6.1, U1.10 (~Y5)
unnamed: R7.1, U1.9 (~Y6)
unnamed: R8.1, U1.7 (~Y7)
unnamed: R10.1, U2.14 (~Y1)
unnamed: R11.1, U2.13 (~Y2)
unnamed: R12.1, U2.12 (~Y3)
unnamed: R13.1, U2.11 (~Y4)
unnamed: R14.1, U2.10 (~Y5)
unnamed: R15.1, U2.9 (~Y6)
unnamed: R16.1, U2.7 (~Y7)
PWM: R32.1, U1.6 (E2), U7.4

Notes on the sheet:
NPNs will invert the inverted outputs

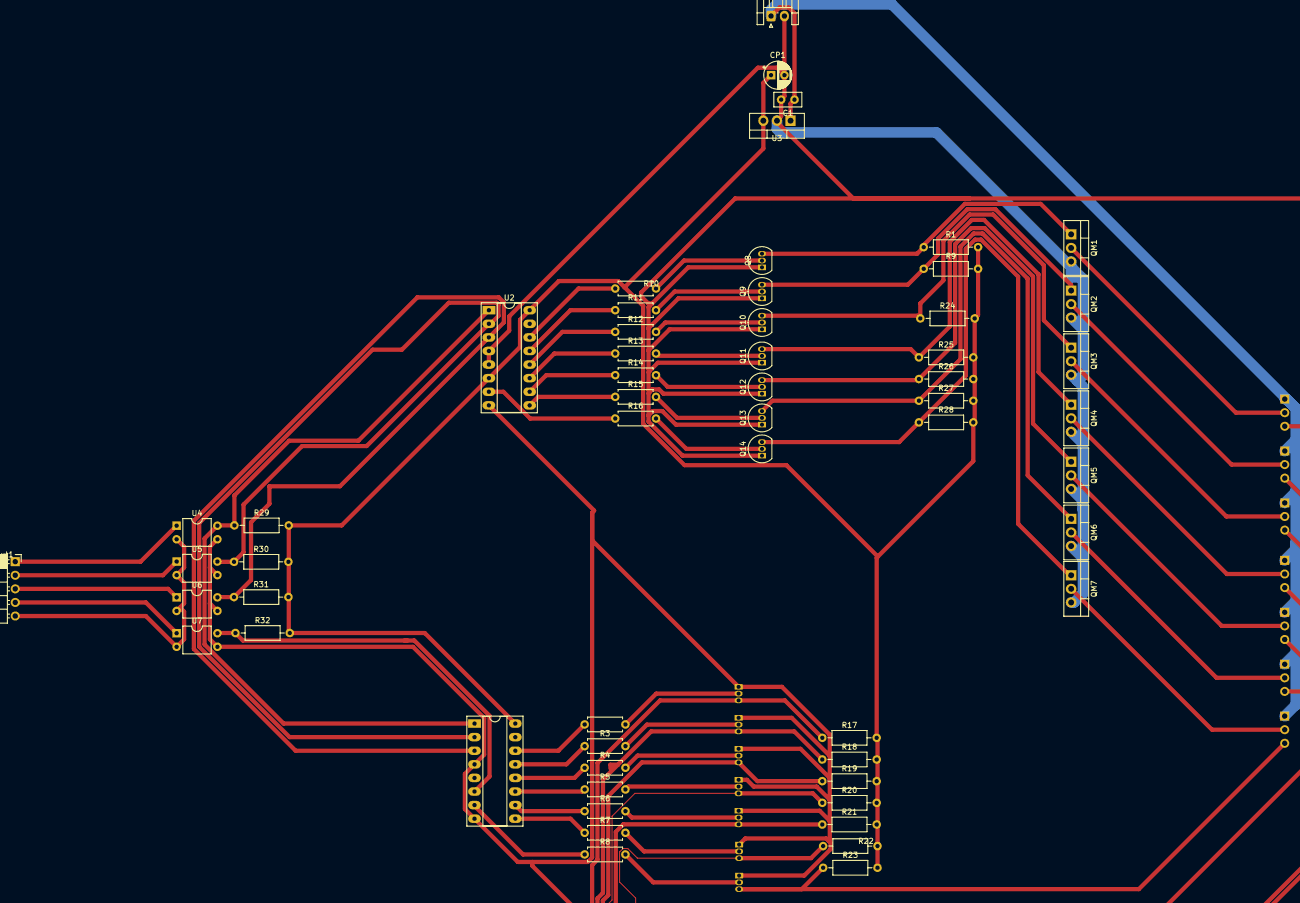
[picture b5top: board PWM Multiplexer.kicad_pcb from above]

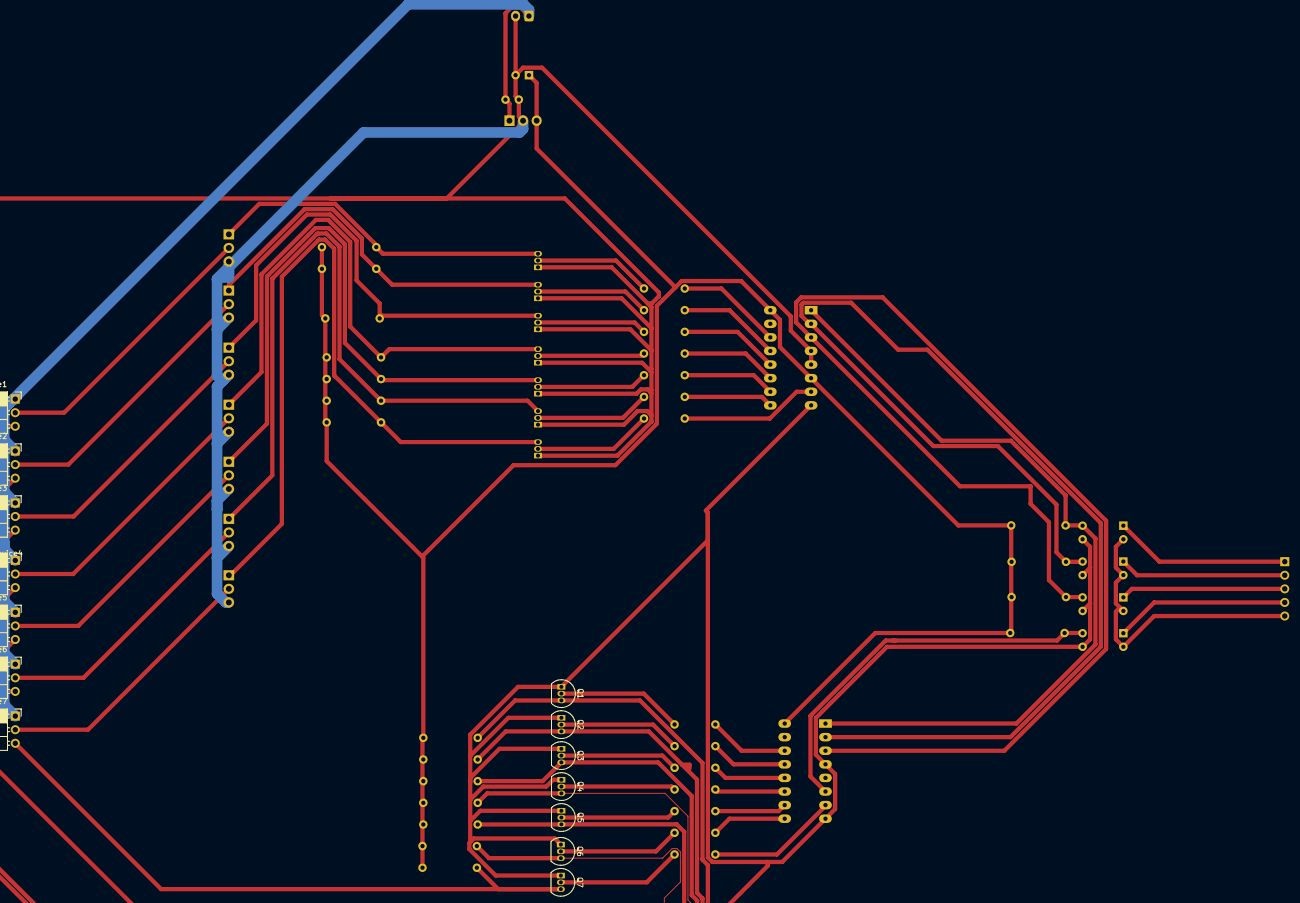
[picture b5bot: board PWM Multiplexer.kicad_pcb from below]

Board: 2 copper layers, 71 parts (14 on the bottom side), 61 nets.
